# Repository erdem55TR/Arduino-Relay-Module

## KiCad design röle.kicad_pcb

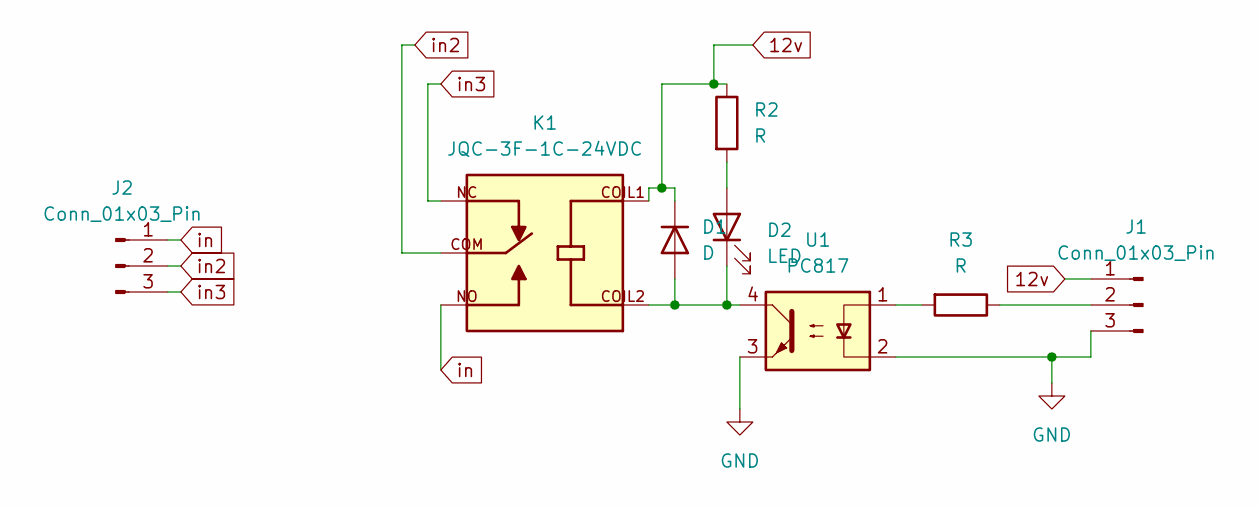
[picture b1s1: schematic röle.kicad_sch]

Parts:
D1: D; D_5W_P10.16mm_Horizontal
D2: LED; LED_D5.0mm_Clear
J1, J2: Conn_01x03_Pin; PhoenixContact_MCV_1,5_3-G-5.08_1x03_P5.08mm_Vertical
K1: JQC-3F-1C-24VDC; RELAY_JQC-3F-1C-24VDC; PARTREV N/A
R2, R3: R; R_Axial_DIN0207_L6.3mm_D2.5mm_P10.16mm_Horizontal
U1: PC817; DIP-4_W7.62mm

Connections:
12v: D1.1 (K), J1.1, K1.COIL1, R2.1
GND: J1.3, U1.2, U1.3
unnamed: D1.2 (A), D2.1 (K), K1.COIL2, U1.4
unnamed: D2.2 (A), R2.2
unnamed: J1.2, R3.1
unnamed: R3.2, U1.1
in: J2.1, K1.NO
in2: J2.2, K1.COM
in3: J2.3, K1.NC

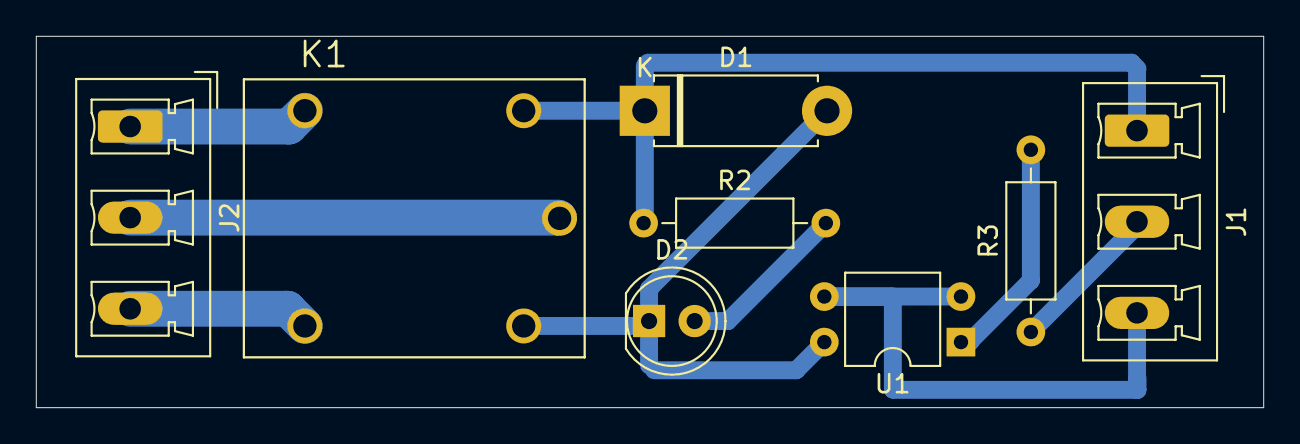
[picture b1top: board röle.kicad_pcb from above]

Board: 2 copper layers, 68.4 x 20.7 mm, 8 parts (0 on the bottom side), 9 nets.
